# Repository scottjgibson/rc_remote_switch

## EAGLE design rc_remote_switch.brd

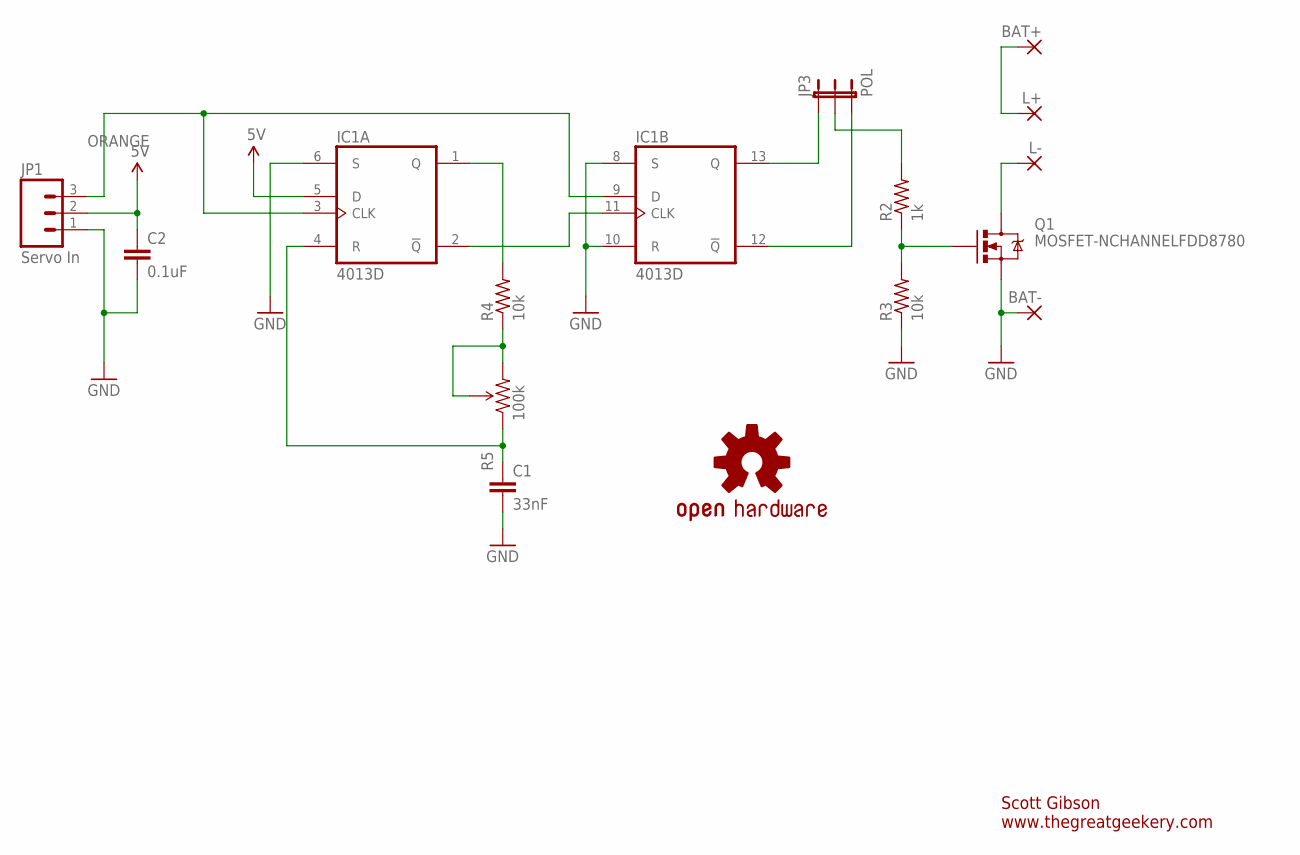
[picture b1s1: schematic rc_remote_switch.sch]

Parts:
BAT+: BAT+; 4,16O1,6
BAT-: BAT-; 4,16O1,6
C1: 33nF; C0805
C2: 0.1uF; C0805
IC1: 4013D; SO14
JP1: Servo In; 1X03
JP3: POL; 1X03
L+: L+; 4,16O1,6
L-: L-; 4,16O1,6
LOGO1: OSHW-LOGOS; OSHW-LOGO-S
Q1: MOSFET-NCHANNELFDD8780; DPAK
R2: 1k; R0805
R3, R4: 10k; R0805
R5: 100k; 3362U-2

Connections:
unnamed: IC1.1 (Q), R4.2
unnamed: IC1.2 (!Q), IC1.11 (CLK)
unnamed: IC1.13 (Q), JP3.1
unnamed: IC1.12 (!Q), JP3.3
unnamed: C1.1, IC1.4 (R), R5.1 (CCW)
unnamed: R4.1, R5.2 (WIPER), R5.3 (CW)
unnamed: Q1.1 (G), R2.1, R3.2
unnamed: JP3.2, R2.2
unnamed: L-.1, Q1.4 (D)
unnamed: BAT+.1, L+.1
ORANGE: IC1.3 (CLK), IC1.9 (D), JP1.3
VDD: BAT-.1, C1.2, C2.2, IC1.6 (S), IC1.8 (S), IC1.10 (R), IC1.14 (VDD), JP1.1, Q1.3 (S), R3.1
VSS: C2.1, IC1.5 (D), IC1.7 (VSS), JP1.2

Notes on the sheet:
Scott Gibson www.thegreatgeekery.com

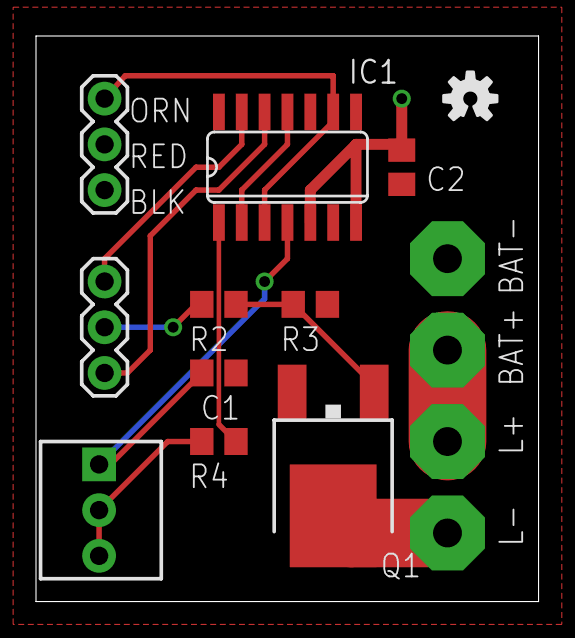
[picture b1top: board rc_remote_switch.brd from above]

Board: 2 copper layers, 27.9 x 31.4 mm, 15 parts (0 on the bottom side), 13 nets.

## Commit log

2013-07-13 Updated Gerber sent for production July 12, 2013

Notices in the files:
parts and their libraries:
SparkFun-DiscreteSemi: Licensing: CC v3.0 Share-Alike You are welcome to use this library for commercial purposes.
